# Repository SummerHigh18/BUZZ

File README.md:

# BUZZ
- A PCB having buttons, LEDs, rotary switch and a BUZZY buzzer!

This is a simple PCB having some buttons and LEDs with a Rotary switch and a buzzer!

# Custom Features
- A Buzzer which buzzes when you press any button or switch!
- A Rotary for controlling the brightness of LEDs

Schematic: 

PCB: 

3D View: 

Firmware: 

**Total Time: ~ 5 hrs**

Reference: Pathfinder 

Used AI only for learning C++.
This can be clearly verified in Lapse.

Lapse: [PCB & Schematic](https://lapse.hackclub.com/timelapse/kYEc9Qr827Vl)
[Firmware](https://lapse.hackclub.com/timelapse/75gp1n5K34I-)

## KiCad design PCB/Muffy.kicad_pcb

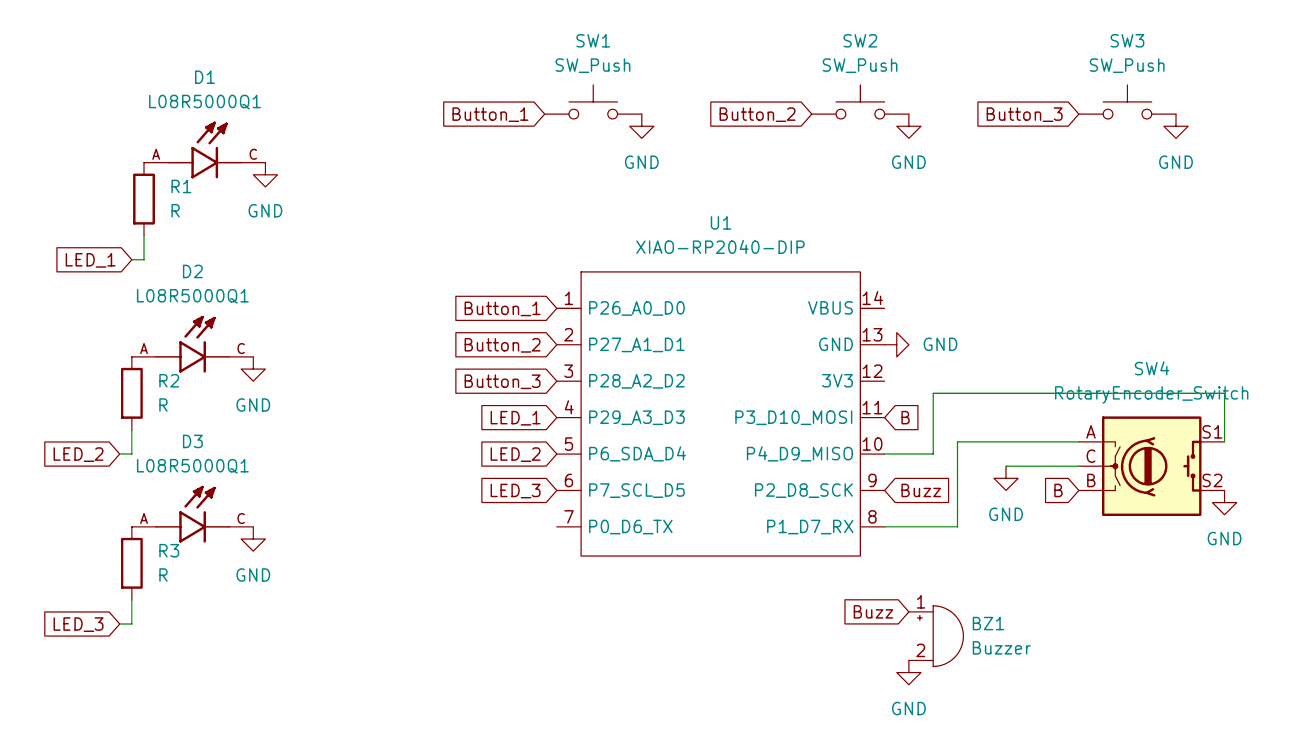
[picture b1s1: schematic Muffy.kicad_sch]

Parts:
BZ1: Buzzer; Buzzer_12x9.5RM7.6
D1, D2, D3: L08R5000Q1; LEDRD254W57D500H1070; PARTREV NA
R1, R2, R3: R; R_Axial_DIN0204_L3.6mm_D1.6mm_P5.08mm_Horizontal
SW1, SW2, SW3: SW_Push; SW_Cherry_MX_1.00u_PCB
SW4: RotaryEncoder_Switch; RotaryEncoder_Alps_EC11E-Switch_Vertical_H20mm_MountingHoles
U1: XIAO-RP2040-DIP

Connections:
B: SW4.B, U1.11 (P3_D10_MOSI)
Button_1: SW1.1, U1.1 (P26_A0_D0)
Button_2: SW2.1, U1.2 (P27_A1_D1)
Button_3: SW3.1, U1.3 (P28_A2_D2)
Buzz: BZ1.1 (+), U1.9 (P2_D8_SCK)
GND: BZ1.2 (-), D1.C, D2.C, D3.C, SW1.2, SW2.2, SW3.2, SW4.C, SW4.S2, U1.13 (GND)
LED_1: R1.2, U1.4 (P29_A3_D3)
LED_2: R2.2, U1.5 (P6_SDA_D4)
LED_3: R3.2, U1.6 (P7_SCL_D5)
unnamed: D1.A, R1.1
unnamed: D2.A, R2.1
unnamed: D3.A, R3.1
unnamed: SW4.A, U1.8 (P1_D7_RX)
unnamed: SW4.S1, U1.10 (P4_D9_MISO)

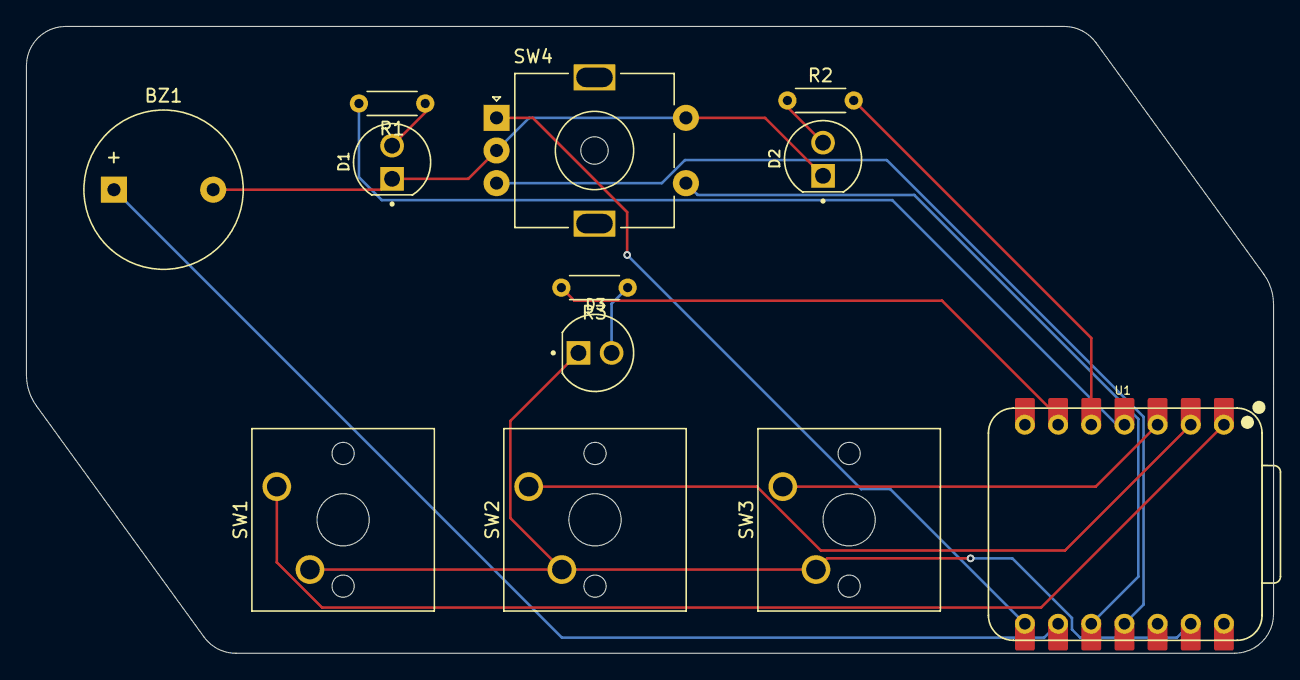
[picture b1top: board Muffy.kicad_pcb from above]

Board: 2 copper layers, 95.5 x 48.0 mm, 12 parts (0 on the bottom side), 14 nets.

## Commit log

2026-03-28 Add project title and description to README
2026-03-28 Updated README and updated JOURNAL with images and time
2026-03-28 Added PCB files
2026-03-28 Fix duplicate sentence in JOURNAL.md
    Corrected duplicate sentence and improved clarity.
2026-03-28 AI Use Case updation
    Added note about using AI for learning C++ and verification in Lapse.
